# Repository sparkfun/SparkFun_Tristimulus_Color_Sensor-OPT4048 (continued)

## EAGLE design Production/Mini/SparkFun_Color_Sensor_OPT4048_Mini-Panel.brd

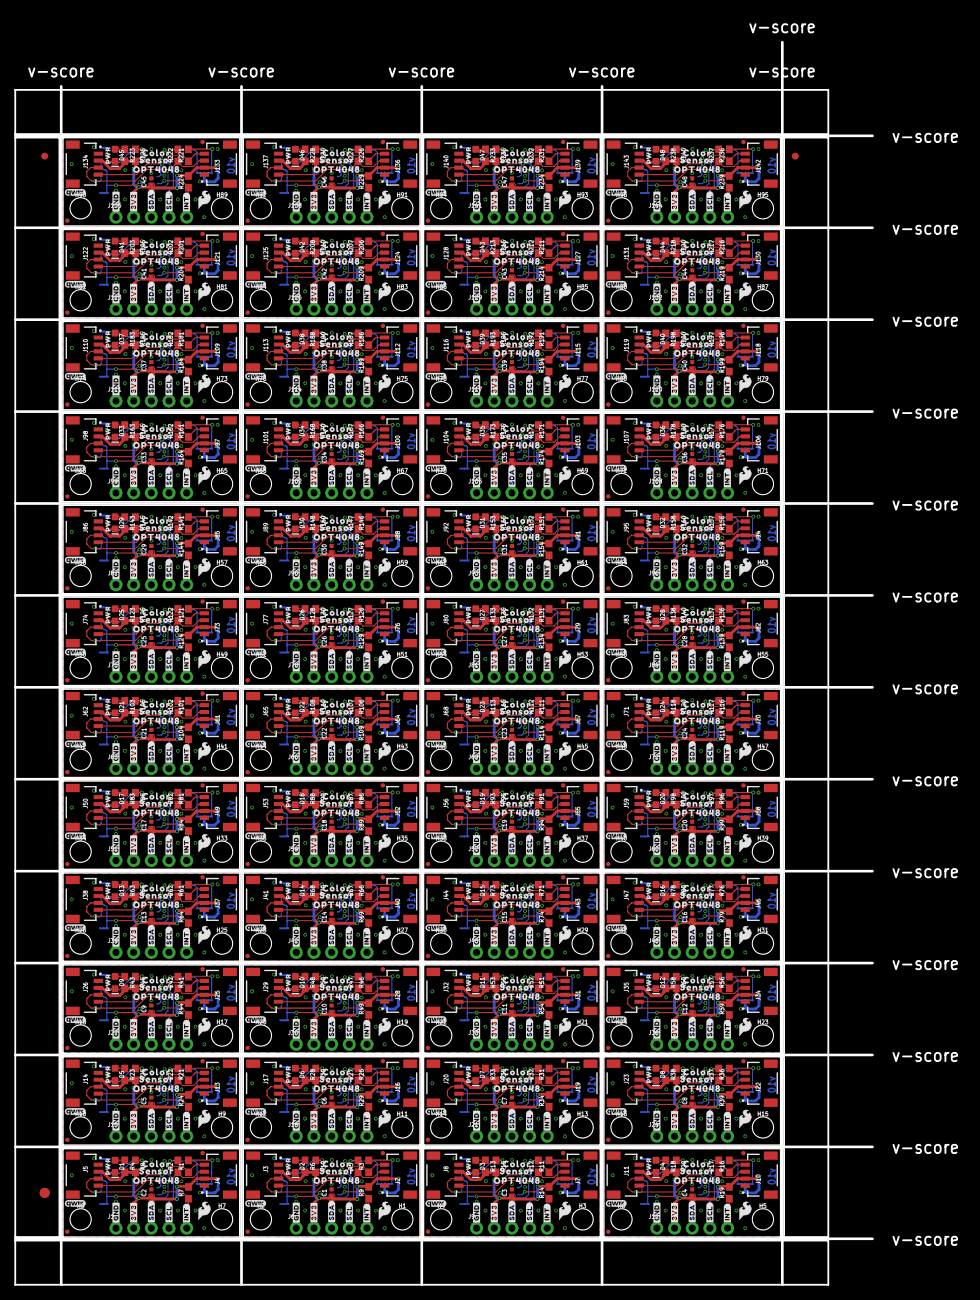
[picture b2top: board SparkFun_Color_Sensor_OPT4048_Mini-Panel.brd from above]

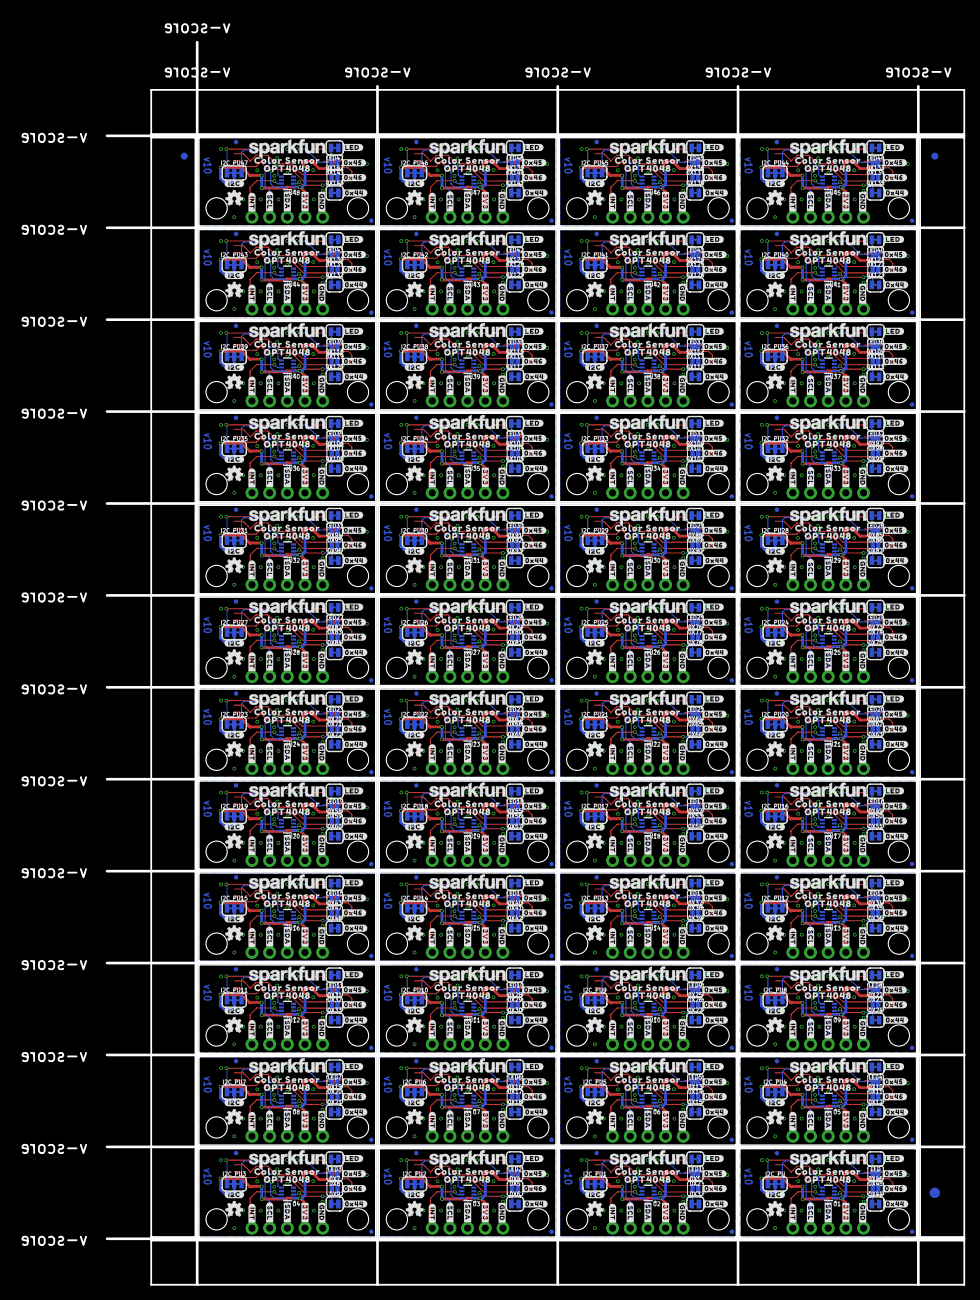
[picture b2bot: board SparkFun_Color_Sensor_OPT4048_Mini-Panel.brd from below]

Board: 2 copper layers, 123.2 x 178.6 mm, 2406 parts (1059 on the bottom side), 528 nets.

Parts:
0X1, 0X2, 0X4, 0X5, 0X7, 0X8, 0X10, 0X11, 0X13, 0X14, 0X16, 0X17, 0X19, 0X20, 0X22, 0X23, 0X25, 0X26, 0X28, 0X29, 0X31, 0X32, 0X34, 0X35, 0X37, 0X38, 0X40, 0X41, 0X43, 0X45, 0X46, 0X47, 0X49, 0X50, 0X52, 0X53, 0X55, 0X56, 0X58, 0X59, 0X61, 0X62, 0X64, 0X65, 0X67, 0X68, 0X70, 0X71, 0X73, 0X74, 0X76, 0X77, 0X79, 0X80, 0X82, 0X83, 0X85, 0X86, 0X88, 0X89, 0X91, 0X92, 0X94, 0X95, 0X97, 0X98, 0X100, 0X101, 0X103, 0X104, 0X106, 0X107, 0X109, 0X110, 0X112, 0X113, 0X115, 0X116, 0X118, 0X119, 0X121, 0X122, 0X124, 0X125, 0X127, 0X128, 0X130, 0X131, 0X133, 0X134, 0X136, 0X137, 0X139, 0X140, 0X142, 0X143: JUMPER-SMT_2_NO_SILK; SMT-JUMPER_2_NO_SILK
0X3, 0X6, 0X9, 0X12, 0X15, 0X18, 0X21, 0X24, 0X27, 0X30, 0X33, 0X36, 0X39, 0X42, 0X44, 0X48, 0X51, 0X54, 0X57, 0X60, 0X63, 0X66, 0X69, 0X72, 0X75, 0X78, 0X81, 0X84, 0X87, 0X90, 0X93, 0X96, 0X99, 0X102, 0X105, 0X108, 0X111, 0X114, 0X117, 0X120, 0X123, 0X126, 0X129, 0X132, 0X135, 0X138, 0X141, 0X144: JUMPER-SMT_2_NC_TRACE_SILK; SMT-JUMPER_2_NC_TRACE_SILK
C1, C2, C3, C4, C5, C6, C7, C8, C9, C10, C11, C12, C13, C14, C15, C16, C17, C18, C19, C20, C21, C22, C23, C24, C25, C26, C27, C28, C29, C30, C31, C32, C33, C34, C35, C36, C37, C38, C39, C40, C41, C42, C43, C44, C45, C46, C47, C48: 0.1uF; 0402-TIGHT
D1, D2, D3, D4, D5, D6, D7, D8, D9, D10, D11, D12, D13, D14, D15, D16, D17, D18, D19, D20, D21, D22, D23, D24, D25, D26, D27, D28, D29, D30, D31, D32, D33, D34, D35, D36, D37, D38, D39, D40, D41, D42, D43, D44, D45, D46, D47, D48: RED; LED-0603
E$1, E$2, E$3, E$4: FIDUCIAL-1X2
E$5, E$6: FIDUCIAL-1.5X3
FD1, FD2, FD3, FD4, FD5, FD6, FD7, FD8, FD9, FD10, FD11, FD12, FD13, FD14, FD15, FD16, FD17, FD18, FD19, FD20, FD21, FD22, FD23, FD24, FD25, FD26, FD27, FD28, FD29, FD30, FD31, FD32, FD33, FD34, FD35, FD36, FD37, FD38, FD39, FD40, FD41, FD42, FD43, FD44, FD45, FD46, FD47, FD48, FD49, FD50, FD51, FD52, FD53, FD54, FD55, FD56, FD57, FD58, FD59, FD60, FD61, FD62, FD63, FD64, FD65, FD66, FD67, FD68, FD69, FD70, FD71, FD72, FD73, FD74, FD75, FD76, FD77, FD78, FD79, FD80, FD81, FD82, FD83, FD84, FD85, FD86, FD87, FD88, FD89, FD90, FD91, FD92, FD93, FD94, FD95, FD96, FD97, FD98, FD99, FD100, FD101, FD102, FD103, FD104, FD105, FD106, FD107, FD108, FD109, FD110, FD111, FD112, FD113, FD114, FD115, FD116, FD117, FD118, FD119, FD120, FD121, FD122, FD123, FD124, FD125, FD126, FD127, FD128, FD129, FD130, FD131, FD132, FD133, FD134, FD135, FD136, FD137, FD138, FD139, FD140, FD141, FD142, FD143, FD144, FD145, FD146, FD147, FD148, FD149, FD150, FD151, FD152, FD153, FD154, FD155, FD156, FD157, FD158, FD159, FD160, FD161, FD162, FD163, FD164, FD165, FD166, FD167, FD168, FD169, FD170, FD171, FD172, FD173, FD174, FD175, FD176, FD177, FD178, FD179, FD180, FD181, FD182, FD183, FD184, FD185, FD186, FD187, FD188, FD189, FD190, FD191, FD192: FIDUCIALUFIDUCIAL; FIDUCIAL-MICRO
FRAME1, FRAME2, FRAME3, FRAME4, FRAME5, FRAME6, FRAME7, FRAME8, FRAME9, FRAME10, FRAME11, FRAME12, FRAME13, FRAME14, FRAME15, FRAME16, FRAME17, FRAME18, FRAME19, FRAME20, FRAME21, FRAME22, FRAME23, FRAME24, FRAME25, FRAME26, FRAME27, FRAME28, FRAME29, FRAME30, FRAME31, FRAME32, FRAME33, FRAME34, FRAME35, FRAME36, FRAME37, FRAME38, FRAME39, FRAME40, FRAME41, FRAME42, FRAME43, FRAME44, FRAME45, FRAME46, FRAME47, FRAME48: FRAME-LETTER; CREATIVE_COMMONS
H1, H2, H3, H4, H5, H6, H7, H8, H9, H10, H11, H12, H13, H14, H15, H16, H17, H18, H19, H20, H21, H22, H23, H24, H25, H26, H27, H28, H29, H30, H31, H32, H33, H34, H35, H36, H37, H38, H39, H40, H41, H42, H43, H44, H45, H46, H47, H48, H49, H50, H51, H52, H53, H54, H55, H56, H57, H58, H59, H60, H61, H62, H63, H64, H65, H66, H67, H68, H69, H70, H71, H72, H73, H74, H75, H76, H77, H78, H79, H80, H81, H82, H83, H84, H85, H86, H87, H88, H89, H90, H91, H92, H93, H94, H95, H96: STAND-OFFTIGHT; STAND-OFF-TIGHT
I2C_PU, I2C_PU1, I2C_PU2, I2C_PU3, I2C_PU4, I2C_PU5, I2C_PU6, I2C_PU7, I2C_PU8, I2C_PU9, I2C_PU10, I2C_PU11, I2C_PU12, I2C_PU13, I2C_PU14, I2C_PU15, I2C_PU16, I2C_PU17, I2C_PU18, I2C_PU19, I2C_PU20, I2C_PU21, I2C_PU22, I2C_PU23, I2C_PU24, I2C_PU25, I2C_PU26, I2C_PU27, I2C_PU28, I2C_PU29, I2C_PU30, I2C_PU31, I2C_PU32, I2C_PU33, I2C_PU34, I2C_PU35, I2C_PU36, I2C_PU37, I2C_PU38, I2C_PU39, I2C_PU40, I2C_PU41, I2C_PU42, I2C_PU43, I2C_PU44, I2C_PU45, I2C_PU46, I2C_PU47: S_MODE; SMT-JUMPER_3_2-NC_TRACE_SILK
J1, J6, J9, J12, J15, J18, J21, J24, J27, J30, J33, J36, J39, J42, J45, J48, J51, J54, J57, J60, J63, J66, J69, J72, J75, J78, J81, J84, J87, J90, J93, J96, J99, J102, J105, J108, J111, J114, J117, J120, J123, J126, J129, J132, J135, J138, J141, J144: 1X05_NO_SILK
J2, J3, J4, J5, J7, J8, J10, J11, J13, J14, J16, J17, J19, J20, J22, J23, J25, J26, J28, J29, J31, J32, J34, J35, J37, J38, J40, J41, J43, J44, J46, J47, J49, J50, J52, J53, J55, J56, J58, J59, J61, J62, J64, J65, J67, J68, J70, J71, J73, J74, J76, J77, J79, J80, J82, J83, J85, J86, J88, J89, J91, J92, J94, J95, J97, J98, J100, J101, J103, J104, J106, J107, J109, J110, J112, J113, J115, J116, J118, J119, J121, J122, J124, J125, J127, J128, J130, J131, J133, J134, J136, J137, J139, J140, J142, J143: QWIIC_RIGHT_ANGLE; JST04_1MM_RA
LED, LED1, LED2, LED3, LED4, LED5, LED6, LED7, LED8, LED9, LED10, LED11, LED12, LED13, LED14, LED15, LED16, LED17, LED18, LED19, LED20, LED21, LED22, LED23, LED24, LED25, LED26, LED27, LED28, LED29, LED30, LED31, LED32, LED33, LED34, LED35, LED36, LED37, LED38, LED39, LED40, LED41, LED42, LED43, LED44, LED45, LED46, LED47: JUMPER-SMT_2_NC_TRACE_SILK; SMT-JUMPER_2_NC_TRACE_SILK
LOGO1, LOGO4, LOGO7, LOGO10, LOGO13, LOGO16, LOGO19, LOGO22, LOGO25, LOGO28, LOGO31, LOGO34, LOGO37, LOGO40, LOGO43, LOGO46, LOGO49, LOGO52, LOGO55, LOGO58, LOGO61, LOGO64, LOGO67, LOGO70, LOGO73, LOGO76, LOGO79, LOGO82, LOGO85, LOGO88, LOGO91, LOGO94, LOGO97, LOGO100, LOGO103, LOGO106, LOGO109, LOGO112, LOGO115, LOGO118, LOGO121, LOGO124, LOGO127, LOGO130, LOGO133, LOGO136, LOGO139, LOGO142: SFE_LOGO_NAMEBLANK; BLANK
LOGO2, LOGO5, LOGO8, LOGO11, LOGO14, LOGO17, LOGO20, LOGO23, LOGO26, LOGO29, LOGO32, LOGO35, LOGO38, LOGO41, LOGO44, LOGO47, LOGO50, LOGO53, LOGO56, LOGO59, LOGO62, LOGO65, LOGO68, LOGO71, LOGO74, LOGO77, LOGO80, LOGO83, LOGO86, LOGO89, LOGO92, LOGO95, LOGO98, LOGO101, LOGO104, LOGO107, LOGO110, LOGO113, LOGO116, LOGO119, LOGO122, LOGO125, LOGO128, LOGO131, LOGO134, LOGO137, LOGO140, LOGO143: QWIIC_LOGO_3MM; QWIIC_3MM
LOGO3, LOGO6, LOGO9, LOGO12, LOGO15, LOGO18, LOGO21, LOGO24, LOGO27, LOGO30, LOGO33, LOGO36, LOGO39, LOGO42, LOGO45, LOGO48, LOGO51, LOGO54, LOGO57, LOGO60, LOGO63, LOGO66, LOGO69, LOGO72, LOGO75, LOGO78, LOGO81, LOGO84, LOGO87, LOGO90, LOGO93, LOGO96, LOGO99, LOGO102, LOGO105, LOGO108, LOGO111, LOGO114, LOGO117, LOGO120, LOGO123, LOGO126, LOGO129, LOGO132, LOGO135, LOGO138, LOGO141, LOGO144: OSHW-LOGONO_SILK; DUMMY
R1, R2, R3, R5, R11, R12, R16, R17, R21, R22, R26, R27, R31, R32, R36, R37, R41, R42, R46, R47, R51, R52, R56, R57, R61, R62, R66, R67, R71, R72, R76, R77, R81, R82, R86, R87, R91, R92, R96, R97, R101, R102, R106, R107, R111, R112, R116, R117, R121, R122, R126, R127, R131, R132, R136, R137, R141, R142, R146, R147, R151, R152, R156, R157, R161, R162, R166, R167, R171, R172, R176, R177, R181, R182, R186, R187, R191, R192, R196, R197, R201, R202, R206, R207, R211, R212, R216, R217, R221, R222, R226, R227, R231, R232, R236, R237: 2.2k; 0603
R4, R6, R13, R18, R23, R28, R33, R38, R43, R48, R53, R58, R63, R68, R73, R78, R83, R88, R93, R98, R103, R108, R113, R118, R123, R128, R133, R138, R143, R148, R153, R158, R163, R168, R173, R178, R183, R188, R193, R198, R203, R208, R213, R218, R223, R228, R233, R238: 4.7k; 0603
R7, R8, R9, R10, R14, R15, R19, R20, R24, R25, R29, R30, R34, R35, R39, R40, R44, R45, R49, R50, R54, R55, R59, R60, R64, R65, R69, R70, R74, R75, R79, R80, R84, R85, R89, R90, R94, R95, R99, R100, R104, R105, R109, R110, R114, R115, R119, R120, R124, R125, R129, R130, R134, R135, R139, R140, R144, R145, R149, R150, R154, R155, R159, R160, R164, R165, R169, R170, R174, R175, R179, R180, R184, R185, R189, R190, R194, R195, R199, R200, R204, R205, R209, R210, R214, R215, R219, R220, R224, R225, R229, R230, R234, R235, R239, R240: 10k; 0603
U1, U2, U3, U4, U5, U6, U7, U8, U9, U10, U11, U12, U13, U14, U15, U16, U17, U18, U19, U20, U21, U22, U23, U24, U25, U26, U27, U28, U29, U30, U31, U32, U33, U34, U35, U36, U37, U38, U39, U40, U41, U42, U43, U44, U45, U46, U47, U48: OPT4048; FCSOT
U$1, U$30, U$60, U$84, U$108, U$132, U$156, U$180, U$204, U$228, U$252, U$276, U$300, U$324, U$348, U$372, U$396, U$420, U$444, U$468, U$492, U$516, U$540, U$564, U$588, U$612, U$636, U$660, U$684, U$708, U$732, U$756, U$780, U$804, U$828, U$852, U$876, U$900, U$924, U$948, U$972, U$996, U$1020, U$1044, U$1068, U$1092, U$1116, U$1140: #INT#9
U$2, U$31, U$61, U$85, U$109, U$133, U$157, U$181, U$205, U$229, U$253, U$277, U$301, U$325, U$349, U$373, U$397, U$421, U$445, U$469, U$493, U$517, U$541, U$565, U$589, U$613, U$637, U$661, U$685, U$709, U$733, U$757, U$781, U$805, U$829, U$853, U$877, U$901, U$925, U$949, U$973, U$997, U$1021, U$1045, U$1069, U$1093, U$1117, U$1141: COLOR_SENSOR227
U$3, U$12, U$32, U$42, U$62, U$67, U$86, U$91, U$110, U$115, U$134, U$139, U$158, U$163, U$182, U$187, U$206, U$211, U$230, U$235, U$254, U$259, U$278, U$283, U$302, U$307, U$326, U$331, U$350, U$355, U$374, U$379, U$398, U$403, U$422, U$427, U$446, U$451, U$470, U$475, U$494, U$499, U$518, U$523, U$542, U$547, U$566, U$571, U$590, U$595, U$614, U$619, U$638, U$643, U$662, U$667, U$686, U$691, U$710, U$715, U$734, U$739, U$758, U$763, U$782, U$787, U$806, U$811, U$830, U$835, U$854, U$859, U$878, U$883, U$902, U$907, U$926, U$931, U$950, U$955, U$974, U$979, U$998, U$1003, U$1022, U$1027, U$1046, U$1051, U$1070, U$1075, U$1094, U$1099, U$1118, U$1123, U$1142, U$1147: OPT4048229
U$4, U$45, U$69, U$93, U$117, U$141, U$165, U$189, U$213, U$237, U$261, U$285, U$309, U$333, U$357, U$381, U$405, U$429, U$453, U$477, U$501, U$525, U$549, U$573, U$597, U$621, U$645, U$669, U$693, U$717, U$741, U$765, U$789, U$813, U$837, U$861, U$885, U$909, U$933, U$957, U$981, U$1005, U$1029, U$1053, U$1077, U$1101, U$1125, U$1149: #0X44#11
U$5, U$46, U$70, U$94, U$118, U$142, U$166, U$190, U$214, U$238, U$262, U$286, U$310, U$334, U$358, U$382, U$406, U$430, U$454, U$478, U$502, U$526, U$550, U$574, U$598, U$622, U$646, U$670, U$694, U$718, U$742, U$766, U$790, U$814, U$838, U$862, U$886, U$910, U$934, U$958, U$982, U$1006, U$1030, U$1054, U$1078, U$1102, U$1126, U$1150: #0X46#11
U$6, U$47, U$71, U$95, U$119, U$143, U$167, U$191, U$215, U$239, U$263, U$287, U$311, U$335, U$359, U$383, U$407, U$431, U$455, U$479, U$503, U$527, U$551, U$575, U$599, U$623, U$647, U$671, U$695, U$719, U$743, U$767, U$791, U$815, U$839, U$863, U$887, U$911, U$935, U$959, U$983, U$1007, U$1031, U$1055, U$1079, U$1103, U$1127, U$1151: #0X45#11
U$7, U$34, U$64, U$88, U$112, U$136, U$160, U$184, U$208, U$232, U$256, U$280, U$304, U$328, U$352, U$376, U$400, U$424, U$448, U$472, U$496, U$520, U$544, U$568, U$592, U$616, U$640, U$664, U$688, U$712, U$736, U$760, U$784, U$808, U$832, U$856, U$880, U$904, U$928, U$952, U$976, U$1000, U$1024, U$1048, U$1072, U$1096, U$1120, U$1144: #INT#3
U$8, U$33, U$63, U$87, U$111, U$135, U$159, U$183, U$207, U$231, U$255, U$279, U$303, U$327, U$351, U$375, U$399, U$423, U$447, U$471, U$495, U$519, U$543, U$567, U$591, U$615, U$639, U$663, U$687, U$711, U$735, U$759, U$783, U$807, U$831, U$855, U$879, U$903, U$927, U$951, U$975, U$999, U$1023, U$1047, U$1071, U$1095, U$1119, U$1143: SFE_LOGO_NAME_.1
U$9, U$36, U$65, U$89, U$113, U$137, U$161, U$185, U$209, U$233, U$257, U$281, U$305, U$329, U$353, U$377, U$401, U$425, U$449, U$473, U$497, U$521, U$545, U$569, U$593, U$617, U$641, U$665, U$689, U$713, U$737, U$761, U$785, U$809, U$833, U$857, U$881, U$905, U$929, U$953, U$977, U$1001, U$1025, U$1049, U$1073, U$1097, U$1121, U$1145: COLOR14
U$10, U$17, U$24, U$37, U$49, U$54, U$73, U$78, U$97, U$102, U$121, U$126, U$145, U$150, U$169, U$174, U$193, U$198, U$217, U$222, U$241, U$246, U$265, U$270, U$289, U$294, U$313, U$318, U$337, U$342, U$361, U$366, U$385, U$390, U$409, U$414, U$433, U$438, U$457, U$462, U$481, U$486, U$505, U$510, U$529, U$534, U$553, U$558, U$577, U$582, U$601, U$606, U$625, U$630, U$649, U$654, U$673, U$678, U$697, U$702, U$721, U$726, U$745, U$750, U$769, U$774, U$793, U$798, U$817, U$822, U$841, U$846, U$865, U$870, U$889, U$894, U$913, U$918, U$937, U$942, U$961, U$966, U$985, U$990, U$1009, U$1014, U$1033, U$1038, U$1057, U$1062, U$1081, U$1086, U$1105, U$1110, U$1129, U$1134: #3V3#0
U$11, U$41, U$66, U$90, U$114, U$138, U$162, U$186, U$210, U$234, U$258, U$282, U$306, U$330, U$354, U$378, U$402, U$426, U$450, U$474, U$498, U$522, U$546, U$570, U$594, U$618, U$642, U$666, U$690, U$714, U$738, U$762, U$786, U$810, U$834, U$858, U$882, U$906, U$930, U$954, U$978, U$1002, U$1026, U$1050, U$1074, U$1098, U$1122, U$1146: SENSOR15
U$13, U$44, U$68, U$92, U$116, U$140, U$164, U$188, U$212, U$236, U$260, U$284, U$308, U$332, U$356, U$380, U$404, U$428, U$452, U$476, U$500, U$524, U$548, U$572, U$596, U$620, U$644, U$668, U$692, U$716, U$740, U$764, U$788, U$812, U$836, U$860, U$884, U$908, U$932, U$956, U$980, U$1004, U$1028, U$1052, U$1076, U$1100, U$1124, U$1148: #SDA#1
U$14, U$48, U$72, U$96, U$120, U$144, U$168, U$192, U$216, U$240, U$264, U$288, U$312, U$336, U$360, U$384, U$408, U$432, U$456, U$480, U$504, U$528, U$552, U$576, U$600, U$624, U$648, U$672, U$696, U$720, U$744, U$768, U$792, U$816, U$840, U$864, U$888, U$912, U$936, U$960, U$984, U$1008, U$1032, U$1056, U$1080, U$1104, U$1128, U$1152: #LED#11
U$15, U$29, U$59, U$83, U$107, U$131, U$155, U$179, U$203, U$227, U$251, U$275, U$299, U$323, U$347, U$371, U$395, U$419, U$443, U$467, U$491, U$515, U$539, U$563, U$587, U$611, U$635, U$659, U$683, U$707, U$731, U$755, U$779, U$803, U$827, U$851, U$875, U$899, U$923, U$947, U$971, U$995, U$1019, U$1043, U$1067, U$1091, U$1115, U$1139: OSHW-LOGO-MINI
U$16, U$18, U$25, U$38, U$50, U$55, U$74, U$79, U$98, U$103, U$122, U$127, U$146, U$151, U$170, U$175, U$194, U$199, U$218, U$223, U$242, U$247, U$266, U$271, U$290, U$295, U$314, U$319, U$338, U$343, U$362, U$367, U$386, U$391, U$410, U$415, U$434, U$439, U$458, U$463, U$482, U$487, U$506, U$511, U$530, U$535, U$554, U$559, U$578, U$583, U$602, U$607, U$626, U$631, U$650, U$655, U$674, U$679, U$698, U$703, U$722, U$727, U$746, U$751, U$770, U$775, U$794, U$799, U$818, U$823, U$842, U$847, U$866, U$871, U$890, U$895, U$914, U$919, U$938, U$943, U$962, U$967, U$986, U$991, U$1010, U$1015, U$1034, U$1039, U$1058, U$1063, U$1082, U$1087, U$1106, U$1111, U$1130, U$1135: #GND#4
U$19, U$21, U$26, U$39, U$51, U$56, U$75, U$80, U$99, U$104, U$123, U$128, U$147, U$152, U$171, U$176, U$195, U$200, U$219, U$224, U$243, U$248, U$267, U$272, U$291, U$296, U$315, U$320, U$339, U$344, U$363, U$368, U$387, U$392, U$411, U$416, U$435, U$440, U$459, U$464, U$483, U$488, U$507, U$512, U$531, U$536, U$555, U$560, U$579, U$584, U$603, U$608, U$627, U$632, U$651, U$656, U$675, U$680, U$699, U$704, U$723, U$728, U$747, U$752, U$771, U$776, U$795, U$800, U$819, U$824, U$843, U$848, U$867, U$872, U$891, U$896, U$915, U$920, U$939, U$944, U$963, U$968, U$987, U$992, U$1011, U$1016, U$1035, U$1040, U$1059, U$1064, U$1083, U$1088, U$1107, U$1112, U$1131, U$1136: #SCL#5
U$20, U$22, U$52, U$76, U$100, U$124, U$148, U$172, U$196, U$220, U$244, U$268, U$292, U$316, U$340, U$364, U$388, U$412, U$436, U$460, U$484, U$508, U$532, U$556, U$580, U$604, U$628, U$652, U$676, U$700, U$724, U$748, U$772, U$796, U$820, U$844, U$868, U$892, U$916, U$940, U$964, U$988, U$1012, U$1036, U$1060, U$1084, U$1108, U$1132: #I2C#11
U$23, U$35, U$53, U$77, U$101, U$125, U$149, U$173, U$197, U$221, U$245, U$269, U$293, U$317, U$341, U$365, U$389, U$413, U$437, U$461, U$485, U$509, U$533, U$557, U$581, U$605, U$629, U$653, U$677, U$701, U$725, U$749, U$773, U$797, U$821, U$845, U$869, U$893, U$917, U$941, U$965, U$989, U$1013, U$1037, U$1061, U$1085, U$1109, U$1133: SFE_LOGO_FLAME_.1
U$27, U$40, U$57, U$81, U$105, U$129, U$153, U$177, U$201, U$225, U$249, U$273, U$297, U$321, U$345, U$369, U$393, U$417, U$441, U$465, U$489, U$513, U$537, U$561, U$585, U$609, U$633, U$657, U$681, U$705, U$729, U$753, U$777, U$801, U$825, U$849, U$873, U$897, U$921, U$945, U$969, U$993, U$1017, U$1041, U$1065, U$1089, U$1113, U$1137: #SDA#6
U$28, U$43, U$58, U$82, U$106, U$130, U$154, U$178, U$202, U$226, U$250, U$274, U$298, U$322, U$346, U$370, U$394, U$418, U$442, U$466, U$490, U$514, U$538, U$562, U$586, U$610, U$634, U$658, U$682, U$706, U$730, U$754, U$778, U$802, U$826, U$850, U$874, U$898, U$922, U$946, U$970, U$994, U$1018, U$1042, U$1066, U$1090, U$1114, U$1138: PWR8821882023

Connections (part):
3.3V: C2.1, I2C_PU.2, J1.2, J4.2, J5.2, R4.2, R7.2, R8.2, U1.P1
3.3V1: C1.1, I2C_PU1.2, J2.2, J3.2, J6.2, R6.2, R9.2, R10.2, U2.P1
3.3V2: C3.1, I2C_PU2.2, J7.2, J8.2, J9.2, R13.2, R14.2, R15.2, U3.P1
3.3V3: C4.1, I2C_PU3.2, J10.2, J11.2, J12.2, R18.2, R19.2, R20.2, U4.P1
3.3V4: C5.1, I2C_PU4.2, J13.2, J14.2, J15.2, R23.2, R24.2, R25.2, U5.P1
3.3V5: C6.1, I2C_PU5.2, J16.2, J17.2, J18.2, R28.2, R29.2, R30.2, U6.P1
3.3V6: C7.1, I2C_PU6.2, J19.2, J20.2, J21.2, R33.2, R34.2, R35.2, U7.P1
3.3V7: C8.1, I2C_PU7.2, J22.2, J23.2, J24.2, R38.2, R39.2, R40.2, U8.P1
3.3V8: C9.1, I2C_PU8.2, J25.2, J26.2, J27.2, R43.2, R44.2, R45.2, U9.P1
3.3V9: C10.1, I2C_PU9.2, J28.2, J29.2, J30.2, R48.2, R49.2, R50.2, U10.P1
3.3V10: C11.1, I2C_PU10.2, J31.2, J32.2, J33.2, R53.2, R54.2, R55.2, U11.P1
3.3V11: C12.1, I2C_PU11.2, J34.2, J35.2, J36.2, R58.2, R59.2, R60.2, U12.P1
3.3V12: C13.1, I2C_PU12.2, J37.2, J38.2, J39.2, R63.2, R64.2, R65.2, U13.P1
3.3V13: C14.1, I2C_PU13.2, J40.2, J41.2, J42.2, R68.2, R69.2, R70.2, U14.P1
3.3V14: C15.1, I2C_PU14.2, J43.2, J44.2, J45.2, R73.2, R74.2, R75.2, U15.P1
3.3V15: C16.1, I2C_PU15.2, J46.2, J47.2, J48.2, R78.2, R79.2, R80.2, U16.P1
3.3V16: C17.1, I2C_PU16.2, J49.2, J50.2, J51.2, R83.2, R84.2, R85.2, U17.P1
3.3V17: C18.1, I2C_PU17.2, J52.2, J53.2, J54.2, R88.2, R89.2, R90.2, U18.P1
3.3V18: C19.1, I2C_PU18.2, J55.2, J56.2, J57.2, R93.2, R94.2, R95.2, U19.P1
3.3V19: C20.1, I2C_PU19.2, J58.2, J59.2, J60.2, R98.2, R99.2, R100.2, U20.P1
3.3V20: C21.1, I2C_PU20.2, J61.2, J62.2, J63.2, R103.2, R104.2, R105.2, U21.P1
3.3V21: C22.1, I2C_PU21.2, J64.2, J65.2, J66.2, R108.2, R109.2, R110.2, U22.P1
3.3V22: C23.1, I2C_PU22.2, J67.2, J68.2, J69.2, R113.2, R114.2, R115.2, U23.P1
3.3V23: C24.1, I2C_PU23.2, J70.2, J71.2, J72.2, R118.2, R119.2, R120.2, U24.P1
3.3V24: C25.1, I2C_PU24.2, J73.2, J74.2, J75.2, R123.2, R124.2, R125.2, U25.P1
3.3V25: C26.1, I2C_PU25.2, J76.2, J77.2, J78.2, R128.2, R129.2, R130.2, U26.P1
3.3V26: C27.1, I2C_PU26.2, J79.2, J80.2, J81.2, R133.2, R134.2, R135.2, U27.P1
3.3V27: C28.1, I2C_PU27.2, J82.2, J83.2, J84.2, R138.2, R139.2, R140.2, U28.P1
3.3V28: C29.1, I2C_PU28.2, J85.2, J86.2, J87.2, R143.2, R144.2, R145.2, U29.P1
3.3V29: C30.1, I2C_PU29.2, J88.2, J89.2, J90.2, R148.2, R149.2, R150.2, U30.P1
3.3V30: C31.1, I2C_PU30.2, J91.2, J92.2, J93.2, R153.2, R154.2, R155.2, U31.P1
3.3V31: C32.1, I2C_PU31.2, J94.2, J95.2, J96.2, R158.2, R159.2, R160.2, U32.P1
3.3V32: C33.1, I2C_PU32.2, J97.2, J98.2, J99.2, R163.2, R164.2, R165.2, U33.P1
3.3V33: C34.1, I2C_PU33.2, J100.2, J101.2, J102.2, R168.2, R169.2, R170.2, U34.P1
3.3V34: C35.1, I2C_PU34.2, J103.2, J104.2, J105.2, R173.2, R174.2, R175.2, U35.P1
3.3V35: C36.1, I2C_PU35.2, J106.2, J107.2, J108.2, R178.2, R179.2, R180.2, U36.P1
3.3V36: C37.1, I2C_PU36.2, J109.2, J110.2, J111.2, R183.2, R184.2, R185.2, U37.P1
3.3V37: C38.1, I2C_PU37.2, J112.2, J113.2, J114.2, R188.2, R189.2, R190.2, U38.P1
3.3V38: C39.1, I2C_PU38.2, J115.2, J116.2, J117.2, R193.2, R194.2, R195.2, U39.P1
3.3V39: C40.1, I2C_PU39.2, J118.2, J119.2, J120.2, R198.2, R199.2, R200.2, U40.P1
3.3V40: C41.1, I2C_PU40.2, J121.2, J122.2, J123.2, R203.2, R204.2, R205.2, U41.P1
3.3V41: C42.1, I2C_PU41.2, J124.2, J125.2, J126.2, R208.2, R209.2, R210.2, U42.P1
3.3V42: C43.1, I2C_PU42.2, J127.2, J128.2, J129.2, R213.2, R214.2, R215.2, U43.P1
3.3V43: C44.1, I2C_PU43.2, J130.2, J131.2, J132.2, R218.2, R219.2, R220.2, U44.P1
3.3V44: C45.1, I2C_PU44.2, J133.2, J134.2, J135.2, R223.2, R224.2, R225.2, U45.P1
3.3V45: C46.1, I2C_PU45.2, J136.2, J137.2, J138.2, R228.2, R229.2, R230.2, U46.P1
3.3V46: C47.1, I2C_PU46.2, J139.2, J140.2, J141.2, R233.2, R234.2, R235.2, U47.P1
3.3V47: C48.1, I2C_PU47.2, J142.2, J143.2, J144.2, R238.2, R239.2, R240.2, U48.P1
ADDR: 0X44.1, 0X45.1, 0X46.1, U1.P2
ADDR1: 0X1.1, 0X2.1, 0X3.1, U2.P2
ADDR2: 0X4.1, 0X5.1, 0X6.1, U3.P2
ADDR3: 0X7.1, 0X8.1, 0X9.1, U4.P2
ADDR4: 0X10.1, 0X11.1, 0X12.1, U5.P2
ADDR5: 0X13.1, 0X14.1, 0X15.1, U6.P2
ADDR6: 0X16.1, 0X17.1, 0X18.1, U7.P2
ADDR7: 0X19.1, 0X20.1, 0X21.1, U8.P2
ADDR8: 0X22.1, 0X23.1, 0X24.1, U9.P2
ADDR9: 0X25.1, 0X26.1, 0X27.1, U10.P2
ADDR10: 0X28.1, 0X29.1, 0X30.1, U11.P2
ADDR11: 0X31.1, 0X32.1, 0X33.1, U12.P2
ADDR12: 0X34.1, 0X35.1, 0X36.1, U13.P2
ADDR13: 0X37.1, 0X38.1, 0X39.1, U14.P2
ADDR14: 0X40.1, 0X41.1, 0X42.1, U15.P2
ADDR15: 0X43.1, 0X47.1, 0X48.1, U16.P2
ADDR16: 0X49.1, 0X50.1, 0X51.1, U17.P2
ADDR17: 0X52.1, 0X53.1, 0X54.1, U18.P2
ADDR18: 0X55.1, 0X56.1, 0X57.1, U19.P2
ADDR19: 0X58.1, 0X59.1, 0X60.1, U20.P2
ADDR20: 0X61.1, 0X62.1, 0X63.1, U21.P2
ADDR21: 0X64.1, 0X65.1, 0X66.1, U22.P2
ADDR22: 0X67.1, 0X68.1, 0X69.1, U23.P2
ADDR23: 0X70.1, 0X71.1, 0X72.1, U24.P2
ADDR24: 0X73.1, 0X74.1, 0X75.1, U25.P2
ADDR25: 0X76.1, 0X77.1, 0X78.1, U26.P2
ADDR26: 0X79.1, 0X80.1, 0X81.1, U27.P2
ADDR27: 0X82.1, 0X83.1, 0X84.1, U28.P2
ADDR28: 0X85.1, 0X86.1, 0X87.1, U29.P2
ADDR29: 0X88.1, 0X89.1, 0X90.1, U30.P2
ADDR30: 0X91.1, 0X92.1, 0X93.1, U31.P2
ADDR31: 0X94.1, 0X95.1, 0X96.1, U32.P2
ADDR32: 0X97.1, 0X98.1, 0X99.1, U33.P2
ADDR33: 0X100.1, 0X101.1, 0X102.1, U34.P2
ADDR34: 0X103.1, 0X104.1, 0X105.1, U35.P2
ADDR35: 0X106.1, 0X107.1, 0X108.1, U36.P2
ADDR36: 0X109.1, 0X110.1, 0X111.1, U37.P2
ADDR37: 0X112.1, 0X113.1, 0X114.1, U38.P2
ADDR38: 0X115.1, 0X116.1, 0X117.1, U39.P2
ADDR39: 0X118.1, 0X119.1, 0X120.1, U40.P2
ADDR40: 0X121.1, 0X122.1, 0X123.1, U41.P2
ADDR41: 0X124.1, 0X125.1, 0X126.1, U42.P2
ADDR42: 0X127.1, 0X128.1, 0X129.1, U43.P2
ADDR43: 0X130.1, 0X131.1, 0X132.1, U44.P2
ADDR44: 0X133.1, 0X134.1, 0X135.1, U45.P2
ADDR45: 0X136.1, 0X137.1, 0X138.1, U46.P2
ADDR46: 0X139.1, 0X140.1, 0X141.1, U47.P2
ADDR47: 0X142.1, 0X143.1, 0X144.1, U48.P2
GND: 0X44.2, C2.2, J1.1, J4.1, J5.1, LED.1, U1.P4
GND1: 0X3.2, C1.2, J2.1, J3.1, J6.1, LED1.1, U2.P4
GND2: 0X6.2, C3.2, J7.1, J8.1, J9.1, LED2.1, U3.P4
GND3: 0X9.2, C4.2, J10.1, J11.1, J12.1, LED3.1, U4.P4
GND4: 0X12.2, C5.2, J13.1, J14.1, J15.1, LED4.1, U5.P4
GND5: 0X15.2, C6.2, J16.1, J17.1, J18.1, LED5.1, U6.P4
GND6: 0X18.2, C7.2, J19.1, J20.1, J21.1, LED6.1, U7.P4
GND7: 0X21.2, C8.2, J22.1, J23.1, J24.1, LED7.1, U8.P4
GND8: 0X24.2, C9.2, J25.1, J26.1, J27.1, LED8.1, U9.P4
GND9: 0X27.2, C10.2, J28.1, J29.1, J30.1, LED9.1, U10.P4
GND10: 0X30.2, C11.2, J31.1, J32.1, J33.1, LED10.1, U11.P4
GND11: 0X33.2, C12.2, J34.1, J35.1, J36.1, LED11.1, U12.P4
GND12: 0X36.2, C13.2, J37.1, J38.1, J39.1, LED12.1, U13.P4
GND13: 0X39.2, C14.2, J40.1, J41.1, J42.1, LED13.1, U14.P4
GND14: 0X42.2, C15.2, J43.1, J44.1, J45.1, LED14.1, U15.P4
GND15: 0X48.2, C16.2, J46.1, J47.1, J48.1, LED15.1, U16.P4
GND16: 0X51.2, C17.2, J49.1, J50.1, J51.1, LED16.1, U17.P4
GND17: 0X54.2, C18.2, J52.1, J53.1, J54.1, LED17.1, U18.P4
GND18: 0X57.2, C19.2, J55.1, J56.1, J57.1, LED18.1, U19.P4
GND19: 0X60.2, C20.2, J58.1, J59.1, J60.1, LED19.1, U20.P4
GND20: 0X63.2, C21.2, J61.1, J62.1, J63.1, LED20.1, U21.P4
GND21: 0X66.2, C22.2, J64.1, J65.1, J66.1, LED21.1, U22.P4
GND22: 0X69.2, C23.2, J67.1, J68.1, J69.1, LED22.1, U23.P4
GND23: 0X72.2, C24.2, J70.1, J71.1, J72.1, LED23.1, U24.P4
GND24: 0X75.2, C25.2, J73.1, J74.1, J75.1, LED24.1, U25.P4
GND25: 0X78.2, C26.2, J76.1, J77.1, J78.1, LED25.1, U26.P4
GND26: 0X81.2, C27.2, J79.1, J80.1, J81.1, LED26.1, U27.P4
GND27: 0X84.2, C28.2, J82.1, J83.1, J84.1, LED27.1, U28.P4
GND28: 0X87.2, C29.2, J85.1, J86.1, J87.1, LED28.1, U29.P4
GND29: 0X90.2, C30.2, J88.1, J89.1, J90.1, LED29.1, U30.P4
GND30: 0X93.2, C31.2, J91.1, J92.1, J93.1, LED30.1, U31.P4
GND31: 0X96.2, C32.2, J94.1, J95.1, J96.1, LED31.1, U32.P4
GND32: 0X99.2, C33.2, J97.1, J98.1, J99.1, LED32.1, U33.P4
GND33: 0X102.2, C34.2, J100.1, J101.1, J102.1, LED33.1, U34.P4
GND34: 0X105.2, C35.2, J103.1, J104.1, J105.1, LED34.1, U35.P4
GND35: 0X108.2, C36.2, J106.1, J107.1, J108.1, LED35.1, U36.P4
GND36: 0X111.2, C37.2, J109.1, J110.1, J111.1, LED36.1, U37.P4
GND37: 0X114.2, C38.2, J112.1, J113.1, J114.1, LED37.1, U38.P4
GND38: 0X117.2, C39.2, J115.1, J116.1, J117.1, LED38.1, U39.P4
GND39: 0X120.2, C40.2, J118.1, J119.1, J120.1, LED39.1, U40.P4
GND40: 0X123.2, C41.2, J121.1, J122.1, J123.1, LED40.1, U41.P4
GND41: 0X126.2, C42.2, J124.1, J125.1, J126.1, LED41.1, U42.P4
GND42: 0X129.2, C43.2, J127.1, J128.1, J129.1, LED42.1, U43.P4
GND43: 0X132.2, C44.2, J130.1, J131.1, J132.1, LED43.1, U44.P4
GND44: 0X135.2, C45.2, J133.1, J134.1, J135.1, LED44.1, U45.P4
GND45: 0X138.2, C46.2, J136.1, J137.1, J138.1, LED45.1, U46.P4
GND46: 0X141.2, C47.2, J139.1, J140.1, J141.1, LED46.1, U47.P4
GND47: 0X144.2, C48.2, J142.1, J143.1, J144.1, LED47.1, U48.P4
INT: J1.5, R7.1, U1.P7
INT1: J6.5, R9.1, U2.P7
INT2: J9.5, R14.1, U3.P7
INT3: J12.5, R19.1, U4.P7
INT4: J15.5, R24.1, U5.P7
INT5: J18.5, R29.1, U6.P7
INT6: J21.5, R34.1, U7.P7
INT7: J24.5, R39.1, U8.P7
INT8: J27.5, R44.1, U9.P7
INT9: J30.5, R49.1, U10.P7
INT10: J33.5, R54.1, U11.P7
INT11: J36.5, R59.1, U12.P7
INT12: J39.5, R64.1, U13.P7
INT13: J42.5, R69.1, U14.P7
INT14: J45.5, R74.1, U15.P7
INT15: J48.5, R79.1, U16.P7
INT16: J51.5, R84.1, U17.P7
INT17: J54.5, R89.1, U18.P7
INT18: J57.5, R94.1, U19.P7
INT19: J60.5, R99.1, U20.P7
INT20: J63.5, R104.1, U21.P7
INT21: J66.5, R109.1, U22.P7
INT22: J69.5, R114.1, U23.P7
INT23: J72.5, R119.1, U24.P7
INT24: J75.5, R124.1, U25.P7
INT25: J78.5, R129.1, U26.P7
INT26: J81.5, R134.1, U27.P7
INT27: J84.5, R139.1, U28.P7
INT28: J87.5, R144.1, U29.P7
INT29: J90.5, R149.1, U30.P7
INT30: J93.5, R154.1, U31.P7
INT31: J96.5, R159.1, U32.P7
INT32: J99.5, R164.1, U33.P7
INT33: J102.5, R169.1, U34.P7
INT34: J105.5, R174.1, U35.P7
INT35: J108.5, R179.1, U36.P7
INT36: J111.5, R184.1, U37.P7
INT37: J114.5, R189.1, U38.P7
INT38: J117.5, R194.1, U39.P7
INT39: J120.5, R199.1, U40.P7
INT40: J123.5, R204.1, U41.P7
INT41: J126.5, R209.1, U42.P7
INT42: J129.5, R214.1, U43.P7
INT43: J132.5, R219.1, U44.P7
INT44: J135.5, R224.1, U45.P7
INT45: J138.5, R229.1, U46.P7
INT46: J141.5, R234.1, U47.P7
INT47: J144.5, R239.1, U48.P7
unnamed: I2C_PU.1, R1.2
unnamed: I2C_PU.3, R2.2
unnamed: D1.A, R4.1
unnamed: D1.C, LED.2
unnamed: I2C_PU1.1, R3.2
unnamed: I2C_PU1.3, R5.2
unnamed: D2.A, R6.1
unnamed: D2.C, LED1.2
unnamed: 0X45.2, R8.1
unnamed: 0X2.2, R10.1
unnamed: I2C_PU2.1, R11.2
unnamed: I2C_PU2.3, R12.2
unnamed: D3.A, R13.1
unnamed: D3.C, LED2.2
unnamed: 0X5.2, R15.1
unnamed: I2C_PU3.1, R16.2
unnamed: I2C_PU3.3, R17.2
unnamed: D4.A, R18.1
unnamed: D4.C, LED3.2
unnamed: 0X8.2, R20.1
unnamed: I2C_PU4.1, R21.2
unnamed: I2C_PU4.3, R22.2
unnamed: D5.A, R23.1
unnamed: D5.C, LED4.2
unnamed: 0X11.2, R25.1
unnamed: I2C_PU5.1, R26.2
unnamed: I2C_PU5.3, R27.2
unnamed: D6.A, R28.1
unnamed: D6.C, LED5.2
unnamed: 0X14.2, R30.1
unnamed: I2C_PU6.1, R31.2
unnamed: I2C_PU6.3, R32.2
unnamed: D7.A, R33.1
unnamed: D7.C, LED6.2
unnamed: 0X17.2, R35.1
unnamed: I2C_PU7.1, R36.2
unnamed: I2C_PU7.3, R37.2
unnamed: D8.A, R38.1
unnamed: D8.C, LED7.2
unnamed: 0X20.2, R40.1
unnamed: I2C_PU8.1, R41.2
unnamed: I2C_PU8.3, R42.2
unnamed: D9.A, R43.1
unnamed: D9.C, LED8.2
unnamed: 0X23.2, R45.1
unnamed: I2C_PU9.1, R46.2
unnamed: I2C_PU9.3, R47.2
unnamed: D10.A, R48.1
unnamed: D10.C, LED9.2
unnamed: 0X26.2, R50.1
unnamed: I2C_PU10.1, R51.2
unnamed: I2C_PU10.3, R52.2
unnamed: D11.A, R53.1
unnamed: D11.C, LED10.2
unnamed: 0X29.2, R55.1
unnamed: I2C_PU11.1, R56.2
unnamed: I2C_PU11.3, R57.2
unnamed: D12.A, R58.1
unnamed: D12.C, LED11.2
unnamed: 0X32.2, R60.1
unnamed: I2C_PU12.1, R61.2
unnamed: I2C_PU12.3, R62.2
unnamed: D13.A, R63.1
unnamed: D13.C, LED12.2
unnamed: 0X35.2, R65.1
unnamed: I2C_PU13.1, R66.2
unnamed: I2C_PU13.3, R67.2
unnamed: D14.A, R68.1
unnamed: D14.C, LED13.2
unnamed: 0X38.2, R70.1
unnamed: I2C_PU14.1, R71.2
unnamed: I2C_PU14.3, R72.2
unnamed: D15.A, R73.1
unnamed: D15.C, LED14.2
unnamed: 0X41.2, R75.1
unnamed: I2C_PU15.1, R76.2
unnamed: I2C_PU15.3, R77.2
unnamed: D16.A, R78.1
unnamed: D16.C, LED15.2
unnamed: 0X47.2, R80.1
unnamed: I2C_PU16.1, R81.2
unnamed: I2C_PU16.3, R82.2
unnamed: D17.A, R83.1
unnamed: D17.C, LED16.2
unnamed: 0X50.2, R85.1
unnamed: I2C_PU17.1, R86.2
unnamed: I2C_PU17.3, R87.2
unnamed: D18.A, R88.1
unnamed: D18.C, LED17.2
unnamed: 0X53.2, R90.1
unnamed: I2C_PU18.1, R91.2
unnamed: I2C_PU18.3, R92.2
unnamed: D19.A, R93.1
unnamed: D19.C, LED18.2
unnamed: 0X56.2, R95.1
unnamed: I2C_PU19.1, R96.2
unnamed: I2C_PU19.3, R97.2
unnamed: D20.A, R98.1
unnamed: D20.C, LED19.2
unnamed: 0X59.2, R100.1
unnamed: I2C_PU20.1, R101.2
unnamed: I2C_PU20.3, R102.2
unnamed: D21.A, R103.1
unnamed: D21.C, LED20.2
unnamed: 0X62.2, R105.1
unnamed: I2C_PU21.1, R106.2
unnamed: I2C_PU21.3, R107.2
unnamed: D22.A, R108.1
unnamed: D22.C, LED21.2
unnamed: 0X65.2, R110.1
unnamed: I2C_PU22.1, R111.2
unnamed: I2C_PU22.3, R112.2
unnamed: D23.A, R113.1
unnamed: D23.C, LED22.2
unnamed: 0X68.2, R115.1
unnamed: I2C_PU23.1, R116.2
unnamed: I2C_PU23.3, R117.2
unnamed: D24.A, R118.1
unnamed: D24.C, LED23.2
unnamed: 0X71.2, R120.1
unnamed: I2C_PU24.1, R121.2
unnamed: I2C_PU24.3, R122.2
unnamed: D25.A, R123.1
unnamed: D25.C, LED24.2
unnamed: 0X74.2, R125.1
unnamed: I2C_PU25.1, R126.2
unnamed: I2C_PU25.3, R127.2
unnamed: D26.A, R128.1
unnamed: D26.C, LED25.2
unnamed: 0X77.2, R130.1
unnamed: I2C_PU26.1, R131.2
unnamed: I2C_PU26.3, R132.2
unnamed: D27.A, R133.1
unnamed: D27.C, LED26.2
unnamed: 0X80.2, R135.1
unnamed: I2C_PU27.1, R136.2
unnamed: I2C_PU27.3, R137.2
unnamed: D28.A, R138.1
unnamed: D28.C, LED27.2
unnamed: 0X83.2, R140.1
unnamed: I2C_PU28.1, R141.2
unnamed: I2C_PU28.3, R142.2
unnamed: D29.A, R143.1
unnamed: D29.C, LED28.2
unnamed: 0X86.2, R145.1
unnamed: I2C_PU29.1, R146.2
unnamed: I2C_PU29.3, R147.2
unnamed: D30.A, R148.1
unnamed: D30.C, LED29.2
unnamed: 0X89.2, R150.1
unnamed: I2C_PU30.1, R151.2
unnamed: I2C_PU30.3, R152.2
unnamed: D31.A, R153.1
unnamed: D31.C, LED30.2
unnamed: 0X92.2, R155.1
unnamed: I2C_PU31.1, R156.2
unnamed: I2C_PU31.3, R157.2
unnamed: D32.A, R158.1
unnamed: D32.C, LED31.2
unnamed: 0X95.2, R160.1
unnamed: I2C_PU32.1, R161.2
unnamed: I2C_PU32.3, R162.2
unnamed: D33.A, R163.1
unnamed: D33.C, LED32.2
unnamed: 0X98.2, R165.1
unnamed: I2C_PU33.1, R166.2
unnamed: I2C_PU33.3, R167.2
unnamed: D34.A, R168.1
unnamed: D34.C, LED33.2
unnamed: 0X101.2, R170.1
unnamed: I2C_PU34.1, R171.2
unnamed: I2C_PU34.3, R172.2
unnamed: D35.A, R173.1
unnamed: D35.C, LED34.2
unnamed: 0X104.2, R175.1
unnamed: I2C_PU35.1, R176.2
unnamed: I2C_PU35.3, R177.2
unnamed: D36.A, R178.1
unnamed: D36.C, LED35.2
unnamed: 0X107.2, R180.1
unnamed: I2C_PU36.1, R181.2
unnamed: I2C_PU36.3, R182.2
unnamed: D37.A, R183.1
unnamed: D37.C, LED36.2
unnamed: 0X110.2, R185.1
unnamed: I2C_PU37.1, R186.2
unnamed: I2C_PU37.3, R187.2
unnamed: D38.A, R188.1
unnamed: D38.C, LED37.2
unnamed: 0X113.2, R190.1
unnamed: I2C_PU38.1, R191.2
unnamed: I2C_PU38.3, R192.2
unnamed: D39.A, R193.1
unnamed: D39.C, LED38.2
unnamed: 0X116.2, R195.1
unnamed: I2C_PU39.1, R196.2
unnamed: I2C_PU39.3, R197.2
unnamed: D40.A, R198.1
unnamed: D40.C, LED39.2
unnamed: 0X119.2, R200.1
unnamed: I2C_PU40.1, R201.2
unnamed: I2C_PU40.3, R202.2
unnamed: D41.A, R203.1
unnamed: D41.C, LED40.2
unnamed: 0X122.2, R205.1
unnamed: I2C_PU41.1, R206.2
unnamed: I2C_PU41.3, R207.2
unnamed: D42.A, R208.1
unnamed: D42.C, LED41.2
unnamed: 0X125.2, R210.1
unnamed: I2C_PU42.1, R211.2
unnamed: I2C_PU42.3, R212.2
unnamed: D43.A, R213.1
unnamed: D43.C, LED42.2
unnamed: 0X128.2, R215.1
unnamed: I2C_PU43.1, R216.2
unnamed: I2C_PU43.3, R217.2
unnamed: D44.A, R218.1
unnamed: D44.C, LED43.2
unnamed: 0X131.2, R220.1
unnamed: I2C_PU44.1, R221.2
unnamed: I2C_PU44.3, R222.2
unnamed: D45.A, R223.1
unnamed: D45.C, LED44.2
unnamed: 0X134.2, R225.1
unnamed: I2C_PU45.1, R226.2
unnamed: I2C_PU45.3, R227.2
unnamed: D46.A, R228.1
unnamed: D46.C, LED45.2
unnamed: 0X137.2, R230.1
unnamed: I2C_PU46.1, R231.2
unnamed: I2C_PU46.3, R232.2
unnamed: D47.A, R233.1
unnamed: D47.C, LED46.2
unnamed: 0X140.2, R235.1
unnamed: I2C_PU47.1, R236.2
unnamed: I2C_PU47.3, R237.2
unnamed: D48.A, R238.1
unnamed: D48.C, LED47.2
unnamed: 0X143.2, R240.1
SCL: J1.4, J4.4, J5.4, R1.1, U1.P5
SCL1: J2.4, J3.4, J6.4, R3.1, U2.P5
SCL2: J7.4, J8.4, J9.4, R11.1, U3.P5
SCL3: J10.4, J11.4, J12.4, R16.1, U4.P5
SCL4: J13.4, J14.4, J15.4, R21.1, U5.P5
SCL5: J16.4, J17.4, J18.4, R26.1, U6.P5
SCL6: J19.4, J20.4, J21.4, R31.1, U7.P5
SCL7: J22.4, J23.4, J24.4, R36.1, U8.P5
SCL8: J25.4, J26.4, J27.4, R41.1, U9.P5
SCL9: J28.4, J29.4, J30.4, R46.1, U10.P5
SCL10: J31.4, J32.4, J33.4, R51.1, U11.P5
SCL11: J34.4, J35.4, J36.4, R56.1, U12.P5
SCL12: J37.4, J38.4, J39.4, R61.1, U13.P5
SCL13: J40.4, J41.4, J42.4, R66.1, U14.P5
SCL14: J43.4, J44.4, J45.4, R71.1, U15.P5
SCL15: J46.4, J47.4, J48.4, R76.1, U16.P5
SCL16: J49.4, J50.4, J51.4, R81.1, U17.P5
SCL17: J52.4, J53.4, J54.4, R86.1, U18.P5
SCL18: J55.4, J56.4, J57.4, R91.1, U19.P5
SCL19: J58.4, J59.4, J60.4, R96.1, U20.P5
SCL20: J61.4, J62.4, J63.4, R101.1, U21.P5
SCL21: J64.4, J65.4, J66.4, R106.1, U22.P5
SCL22: J67.4, J68.4, J69.4, R111.1, U23.P5
SCL23: J70.4, J71.4, J72.4, R116.1, U24.P5
SCL24: J73.4, J74.4, J75.4, R121.1, U25.P5
SCL25: J76.4, J77.4, J78.4, R126.1, U26.P5
SCL26: J79.4, J80.4, J81.4, R131.1, U27.P5
SCL27: J82.4, J83.4, J84.4, R136.1, U28.P5
SCL28: J85.4, J86.4, J87.4, R141.1, U29.P5
SCL29: J88.4, J89.4, J90.4, R146.1, U30.P5
SCL30: J91.4, J92.4, J93.4, R151.1, U31.P5
SCL31: J94.4, J95.4, J96.4, R156.1, U32.P5
SCL32: J97.4, J98.4, J99.4, R161.1, U33.P5
SCL33: J100.4, J101.4, J102.4, R166.1, U34.P5
SCL34: J103.4, J104.4, J105.4, R171.1, U35.P5
SCL35: J106.4, J107.4, J108.4, R176.1, U36.P5
SCL36: J109.4, J110.4, J111.4, R181.1, U37.P5
SCL37: J112.4, J113.4, J114.4, R186.1, U38.P5
SCL38: J115.4, J116.4, J117.4, R191.1, U39.P5
SCL39: J118.4, J119.4, J120.4, R196.1, U40.P5
SCL40: J121.4, J122.4, J123.4, R201.1, U41.P5
SCL41: J124.4, J125.4, J126.4, R206.1, U42.P5
SCL42: J127.4, J128.4, J129.4, R211.1, U43.P5
SCL43: J130.4, J131.4, J132.4, R216.1, U44.P5
SCL44: J133.4, J134.4, J135.4, R221.1, U45.P5
SCL45: J136.4, J137.4, J138.4, R226.1, U46.P5
SCL46: J139.4, J140.4, J141.4, R231.1, U47.P5
SCL47: J142.4, J143.4, J144.4, R236.1, U48.P5
SDA: 0X46.2, J1.3, J4.3, J5.3, R2.1, U1.P8
SDA1: 0X1.2, J2.3, J3.3, J6.3, R5.1, U2.P8
SDA2: 0X4.2, J7.3, J8.3, J9.3, R12.1, U3.P8
SDA3: 0X7.2, J10.3, J11.3, J12.3, R17.1, U4.P8
SDA4: 0X10.2, J13.3, J14.3, J15.3, R22.1, U5.P8
SDA5: 0X13.2, J16.3, J17.3, J18.3, R27.1, U6.P8
SDA6: 0X16.2, J19.3, J20.3, J21.3, R32.1, U7.P8
SDA7: 0X19.2, J22.3, J23.3, J24.3, R37.1, U8.P8
SDA8: 0X22.2, J25.3, J26.3, J27.3, R42.1, U9.P8
SDA9: 0X25.2, J28.3, J29.3, J30.3, R47.1, U10.P8
SDA10: 0X28.2, J31.3, J32.3, J33.3, R52.1, U11.P8
SDA11: 0X31.2, J34.3, J35.3, J36.3, R57.1, U12.P8
SDA12: 0X34.2, J37.3, J38.3, J39.3, R62.1, U13.P8
SDA13: 0X37.2, J40.3, J41.3, J42.3, R67.1, U14.P8
SDA14: 0X40.2, J43.3, J44.3, J45.3, R72.1, U15.P8
SDA15: 0X43.2, J46.3, J47.3, J48.3, R77.1, U16.P8
SDA16: 0X49.2, J49.3, J50.3, J51.3, R82.1, U17.P8
SDA17: 0X52.2, J52.3, J53.3, J54.3, R87.1, U18.P8
SDA18: 0X55.2, J55.3, J56.3, J57.3, R92.1, U19.P8
SDA19: 0X58.2, J58.3, J59.3, J60.3, R97.1, U20.P8
SDA20: 0X61.2, J61.3, J62.3, J63.3, R102.1, U21.P8
SDA21: 0X64.2, J64.3, J65.3, J66.3, R107.1, U22.P8
SDA22: 0X67.2, J67.3, J68.3, J69.3, R112.1, U23.P8
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
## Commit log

2023-06-12 Removes micro outline, adds mini outline
2023-06-12 Adds OPT4048 device, adds to Qwiic board
2023-06-13 Routes the Qwiic board
2023-06-13 Routes Qwiic board
    * Adds ADDR2 jumper for SDA
2023-06-14 Improves ground pour
    * Improves schematic aesthetic
2023-06-14 Finishes routing Qwiic mini
    * Adds silk to Qwiic mini
    * Adds ordering instructions
2023-06-16 Changes Jumper selection, moves resistors away from IC, and changes decoupling cap to smaller package
2023-06-16 Adds some restrict near the ground pin for better ground pour
2023-06-16 Changes address selection on the mini
2023-06-16 Places version number on the bottom out from under the Qwiic connector
2023-06-16 Approves some DRC errors
2023-06-16 Fixes some traces
2023-06-16 Adds correct red LEDs and their resistors, updates PROD_ID for part.
2023-06-16 Fixes SKU in designs, some DRC errors
    * Adds proto gerbers
2023-07-19 Rolls version
2023-07-19 Adds jumper to interrupt pin on both designs
2023-07-19 Revert "Adds jumper to interrupt pin on both designs"
    This reverts commit a39334068ad88ec2875ce3e39fad74091b9d5839.
2023-07-21 Adds PCB version to panel zip file
2023-07-21 Adds second Qwiic label, spins version number
2023-07-21 Adds production files
2023-07-26 Initial pass of documentation
2023-08-03 Initial pass of docs
2023-08-09 Update of code
2023-08-14 Updated intro and resources
2023-08-14 Update mkdocs.yml
    Adding typeset
2023-08-25 Update to images and Hardware Overview
2023-08-25 Updating mini image sizes
2023-08-28 Minor changes to hardware overview
2023-08-28 Adding Hardware Assembly images
2023-08-28 Update software_setup.md
    Adding correct library
2023-08-29 Update to introduction
2023-08-29 Verbiage changes
2023-08-29 Updating links for eagle files
2023-08-30 Updating Example 3 image
2023-08-31 Adding link to CIE space to example 1
2023-09-05 Example 5 images and code
2023-09-06 Adding soldered assembly
2023-09-07 Updating descriptions of each example and adding ex 5 setup photo
2023-09-20 Update to example 3
2023-09-20 Fixing image
2023-09-21 Update description
2023-09-21 Deployed 3e37171 with MkDocs version: 1.5.3
2025-01-08 Update file_issue.md
    fixed broken link
2026-06-03 Deployed e9f300b with MkDocs version: 1.6.1
